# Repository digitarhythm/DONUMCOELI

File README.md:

# DONUMCOELI
Triple Rotary encoder Keyboard GL516 Tenkeyless 40percent 'DONUMCOELI'

# Firmware
https://github.com/digitarhythm/qmk_firmware/tree/donumcoeli/keyboards/trek/donumcoeli

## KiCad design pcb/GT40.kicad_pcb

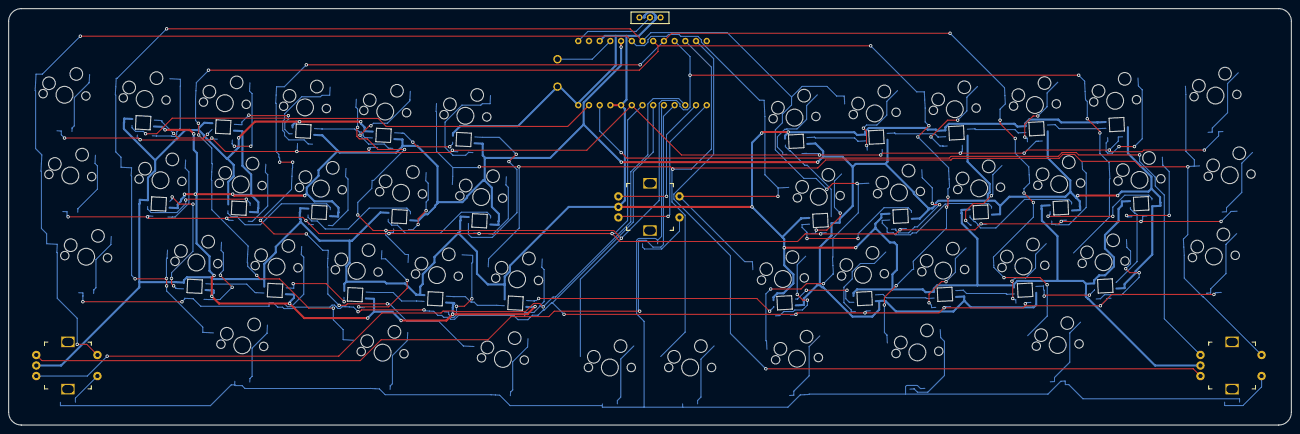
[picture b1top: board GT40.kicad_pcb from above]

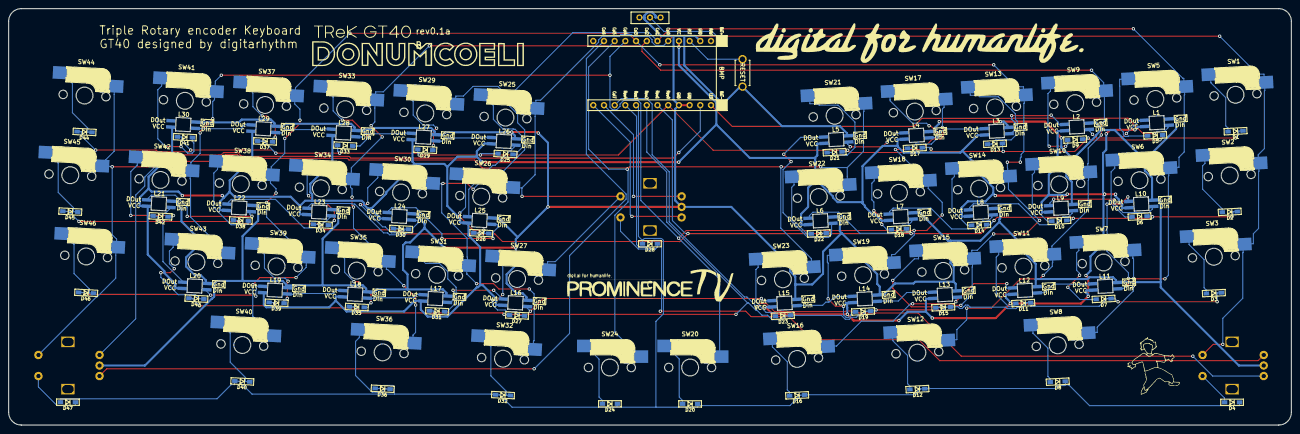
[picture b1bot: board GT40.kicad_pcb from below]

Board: 2 copper layers, 304.4 x 98.8 mm, 131 parts (4 on the bottom side), 97 nets.

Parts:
A: LOGO
B: LOGO
C: LOGO
D: LOGO
D1, D2, D3, D4, D5, D6, D7, D8, D9, D10, D11, D12, D13, D14, D15, D16, D17, D18, D19, D20, D21, D22, D23, D24, D25, D26, D27, D28, D29, D30, D31, D32, D33, D34, D35, D36, D37, D38, D39, D40, D41, D42, D43, D44, D45, D46, D47: D; Diode_SMD
J1: Conn_01x02; Battery_XH2.5_GL_PCB
L1, L2, L3, L4, L5, L6, L7, L8, L9, L10, L11, L12, L13, L14, L15, L16, L17, L18, L19, L20, L21, L22, L23, L24, L25, L26, L27, L28, L29, L30: SK6812MINI; LED_SK6812MINI-E_BL
SW1, SW5, SW6, SW7, SW9, SW10, SW11, SW13, SW14, SW15, SW17, SW18, SW19, SW20, SW21, SW22, SW23, SW24, SW25, SW26, SW27, SW29, SW30, SW31, SW33, SW34, SW35, SW37, SW38, SW39, SW41, SW42, SW43: SW_PUSH; CherryMX_Hotswap_1u
SW2, SW8, SW16, SW32, SW40, SW45: SW_PUSH; CherryMX_Hotswap_1.25u
SW3, SW12, SW36, SW46: SW_PUSH; CherryMX_Hotswap_1.75u
SW4, SW28, SW47: RotaryEncoder_Switch; RotaryEncoder_EC12E
SW44: SW_PUSH; CherryMX_Hotswap_1.5u
SW48: SW_PUSH; ResetSW
U1: BLEMicroPro; Micon_BMP_GL

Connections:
Bat+: J1.1, U1.25 (BAT+)
Col0: SW1.1, SW2.1, SW3.1, SW4.S2, SW25.1, SW26.1, SW27.1, SW28.S2, U1.20 (F4/PIN20)
Col1: SW5.1, SW6.1, SW7.1, SW8.1, SW29.1, SW30.1, SW31.1, SW32.1, U1.19 (F5/PIN19)
Col2: SW9.1, SW10.1, SW11.1, SW12.1, SW33.1, SW34.1, SW35.1, SW36.1, U1.18 (F6/PIN18)
Col3: SW13.1, SW14.1, SW15.1, SW16.1, SW37.1, SW38.1, SW39.1, SW40.1, U1.17 (F7/PIN17)
Col4: SW17.1, SW18.1, SW19.1, SW20.1, SW41.1, SW42.1, SW43.1, U1.16 (B1/PIN16)
Col5: SW21.1, SW22.1, SW23.1, SW24.1, SW44.1, SW45.1, SW46.1, SW47.S2, U1.15 (B3/PIN15)
GND: J1.2, L1.2 (VSS), L2.2 (VSS), L3.2 (VSS), L4.2 (VSS), L5.2 (VSS), L6.2 (VSS), L7.2 (VSS), L8.2 (VSS), L9.2 (VSS), L10.2 (VSS), L11.2 (VSS), L12.2 (VSS), L13.2 (VSS), L14.2 (VSS), L15.2 (VSS), L16.2 (VSS), L17.2 (VSS), L18.2 (VSS), L19.2 (VSS), L20.2 (VSS), L21.2 (VSS), L22.2 (VSS), L23.2 (VSS), L24.2 (VSS), L25.2 (VSS), L26.2 (VSS), L27.2 (VSS), L28.2 (VSS), L29.2 (VSS), L30.2 (VSS), SW4.C, SW28.C, SW47.C, SW48.2, U1.3 (GND), U1.4 (GND), U1.23 (GND), U1.26 (BAT-)
LED: L1.3 (DIN), U1.1 (D3/PIN1)
unnamed: D1.2 (A), SW1.2
unnamed: D2.2 (A), SW2.2
unnamed: D3.2 (A), SW3.2
unnamed: D4.2 (A), SW4.S1
unnamed: D5.2 (A), SW5.2
unnamed: D6.2 (A), SW6.2
unnamed: D7.2 (A), SW7.2
unnamed: D8.2 (A), SW8.2
unnamed: D9.2 (A), SW9.2
unnamed: D10.2 (A), SW10.2
unnamed: D11.2 (A), SW11.2
unnamed: D12.2 (A), SW12.2
unnamed: D13.2 (A), SW13.2
unnamed: D14.2 (A), SW14.2
unnamed: D15.2 (A), SW15.2
unnamed: D16.2 (A), SW16.2
unnamed: D17.2 (A), SW17.2
unnamed: D18.2 (A), SW18.2
unnamed: D19.2 (A), SW19.2
unnamed: D20.2 (A), SW20.2
unnamed: D21.2 (A), SW21.2
unnamed: D22.2 (A), SW22.2
unnamed: D23.2 (A), SW23.2
unnamed: D24.2 (A), SW24.2
unnamed: D25.1 (K), SW25.2
unnamed: D26.1 (K), SW26.2
unnamed: D27.1 (K), SW27.2
unnamed: D28.1 (K), SW28.S1
unnamed: D29.1 (K), SW29.2
unnamed: D30.1 (K), SW30.2
unnamed: D31.1 (K), SW31.2
unnamed: D32.1 (K), SW32.2
unnamed: D33.1 (K), SW33.2
unnamed: D34.1 (K), SW34.2
unnamed: D35.1 (K), SW35.2
unnamed: D36.1 (K), SW36.2
unnamed: D37.1 (K), SW37.2
unnamed: D38.1 (K), SW38.2
unnamed: D39.1 (K), SW39.2
unnamed: D40.1 (K), SW40.2
unnamed: D41.1 (K), SW41.2
unnamed: D42.1 (K), SW42.2
unnamed: D43.1 (K), SW43.2
unnamed: D44.1 (K), SW44.2
unnamed: D45.1 (K), SW45.2
unnamed: D46.1 (K), SW46.2
unnamed: D47.1 (K), SW47.S1
unnamed: L1.1 (DOUT), L2.3 (DIN)
unnamed: L2.1 (DOUT), L3.3 (DIN)
unnamed: L3.1 (DOUT), L4.3 (DIN)
unnamed: L4.1 (DOUT), L5.3 (DIN)
unnamed: L5.1 (DOUT), L6.3 (DIN)
unnamed: L6.1 (DOUT), L7.3 (DIN)
unnamed: L7.1 (DOUT), L8.3 (DIN)
unnamed: L8.1 (DOUT), L9.3 (DIN)
unnamed: L10.1 (DOUT), L11.3 (DIN)
unnamed: L9.1 (DOUT), L10.3 (DIN)
unnamed: L11.1 (DOUT), L12.3 (DIN)
unnamed: L12.1 (DOUT), L13.3 (DIN)
unnamed: L13.1 (DOUT), L14.3 (DIN)
unnamed: L14.1 (DOUT), L15.3 (DIN)
unnamed: L15.1 (DOUT), L16.3 (DIN)
unnamed: L16.1 (DOUT), L17.3 (DIN)
unnamed: L17.1 (DOUT), L18.3 (DIN)
unnamed: L18.1 (DOUT), L19.3 (DIN)
unnamed: L19.1 (DOUT), L20.3 (DIN)
unnamed: L20.1 (DOUT), L21.3 (DIN)
unnamed: L21.1 (DOUT), L22.3 (DIN)
unnamed: L22.1 (DOUT), L23.3 (DIN)
unnamed: L23.1 (DOUT), L24.3 (DIN)
unnamed: L24.1 (DOUT), L25.3 (DIN)
unnamed: L25.1 (DOUT), L26.3 (DIN)
unnamed: L26.1 (DOUT), L27.3 (DIN)
unnamed: L27.1 (DOUT), L28.3 (DIN)
unnamed: L28.1 (DOUT), L29.3 (DIN)
unnamed: L29.1 (DOUT), L30.3 (DIN)
RE1a: SW4.A, U1.9 (D7/PIN9)
RE1b: SW4.B, U1.10 (E6/PIN10)
RE2a: SW28.A, U1.11 (B4/PIN11)
RE2b: SW28.B, U1.12 (B5/PIN12)
RE3a: SW47.A, U1.2 (D2/PIN2)
RE3b: SW47.B, U1.14 (B2/PIN14)
Reset: SW48.1, U1.22 (RST)
Row0: D1.1 (K), D5.1 (K), D9.1 (K), D13.1 (K), D17.1 (K), D21.1 (K), D25.2 (A), D29.2 (A), D33.2 (A), D37.2 (A), D41.2 (A), D44.2 (A), U1.5 (D1/PIN5/SDA)
Row1: D2.1 (K), D6.1 (K), D10.1 (K), D14.1 (K), D18.1 (K), D22.1 (K), D26.2 (A), D30.2 (A), D34.2 (A), D38.2 (A), D42.2 (A), D45.2 (A), U1.6 (D0/PIN6/SCL)
Row2: D3.1 (K), D7.1 (K), D11.1 (K), D15.1 (K), D19.1 (K), D23.1 (K), D27.2 (A), D31.2 (A), D35.2 (A), D39.2 (A), D43.2 (A), D46.2 (A), U1.7 (D4/PIN7)
Row3: D4.1 (K), D8.1 (K), D12.1 (K), D16.1 (K), D20.1 (K), D24.1 (K), D28.2 (A), D32.2 (A), D36.2 (A), D40.2 (A), D47.2 (A), U1.8 (C6/PIN8)
VCC: L1.4 (VDD), L2.4 (VDD), L3.4 (VDD), L4.4 (VDD), L5.4 (VDD), L6.4 (VDD), L7.4 (VDD), L8.4 (VDD), L9.4 (VDD), L10.4 (VDD), L11.4 (VDD), L12.4 (VDD), L13.4 (VDD), L14.4 (VDD), L15.4 (VDD), L16.4 (VDD), L17.4 (VDD), L18.4 (VDD), L19.4 (VDD), L20.4 (VDD), L21.4 (VDD), L22.4 (VDD), L23.4 (VDD), L24.4 (VDD), L25.4 (VDD), L26.4 (VDD), L27.4 (VDD), L28.4 (VDD), L29.4 (VDD), L30.4 (VDD), U1.21 (VCC)

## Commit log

2024-01-30 update licence file
2024-02-25 Update LICENCE
